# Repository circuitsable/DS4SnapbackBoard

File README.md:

# DS4SnapbackBoard

This is a PCB that latches onto the bottom of your joysticks on a DualShock 4 intended to get rid of controller snapback.

# Why/About

Never heard of snapback? Here is a [video](https://www.youtube.com/watch?v=O4rigBTxgPM) describing it and why it is a problem.

I designed this because several of my DS4 controllers have had issues with snapback and the issues it entails, and because I prefered a cleaner result than through hole ceramic capacitors lying on the back of my controller's PCB. It connects the signal & ground pins of each axis' potentiometer to dampen the oscillations of the snapback.

This mod uses 0805 1uF ceramic SMD capacitors, since I wanted to make the capacitors somewhat easy to install and 1uF is a good catchall value to stop snapback. Different boards for different capacitor sizes can very easily be made, make an issue for a different size if you would like one.

This mod should not require much experience soldering, but if the capacitor size is too small, create an issue on this repo requesting a bigger size. Editing the PCB yourself to use bigger capacitors should be very easy as well.

# What you'll need

The PCB, of which gerbers are available for in the [releases](https://github.com/circuitsable/DS4SnapbackBoard/releases/tag/gerbers). The thinner you can make the PCB, the better, 0.8mm is a good thickness. The PCB can be ordered from any board house, but some may not like the castellated holes or charge extra for them. [Oshpark](https://oshpark.com/#services) will do castilated holes, has 0.8mm availability and is quite cheap, but the finished boards may require post processing with a small knife.

2 0805 1uF SMD Ceramic Capacitors. Their voltage rating does not matter. They can be sourced from anywhere, here are some examples: [Aliexpress](https://www.aliexpress.us/item/2251832778239041.html), [Ebay](https://www.ebay.com/itm/195680390537), [Mouser](https://www.mouser.com/ProductDetail/Samsung-Electro-Mechanics/CL21B105KPFNNNE?qs=349EhDEZ59rb3V94UrmRdQ%3D%3D)

Basic soldering equipment.

Hobby knife.

# Installation

Touch up the castilated holes of your PCB, as they will most certainly arrive with excess material from the pads being drilled. Solder the capacitors to their two available footprints on the PCB, align the PCB in the middle of the joystick footprint on the back of your DS4 board, solder the 4 big pads first to keep the board in alignment, then solder the pads to the actual potentiometer legs of the joysticks.

# PCB Images

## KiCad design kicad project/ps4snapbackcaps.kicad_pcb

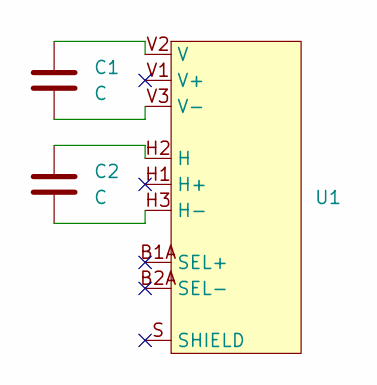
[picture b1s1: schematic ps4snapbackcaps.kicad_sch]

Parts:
C1, C2: C; C_0805_2012Metric_Pad1.18x1.45mm_HandSolder
U1: PS4_joystick

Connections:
unnamed: C2.1, U1.H2 (H)
unnamed: C2.2, U1.H3 (H-)
unnamed: C1.1, U1.V2 (V)
unnamed: C1.2, U1.V3 (V-)

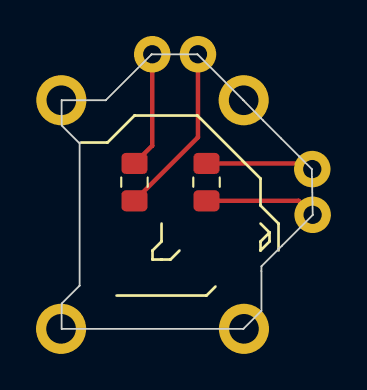
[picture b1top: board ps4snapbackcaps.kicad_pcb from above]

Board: 2 copper layers, 14.0 x 15.2 mm, 3 parts (1 on the bottom side), 4 nets.

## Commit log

2024-04-14 Update ReadMe again
2024-04-14 Added images
2024-04-14 Update ReadMe to actually display images
2024-04-14 Add more images
2024-04-14 update images
2024-04-14 add gerbers
2024-04-14 add kicad design filex
2024-04-14 update kicad design files
2024-04-16 update gerbers
2024-04-30 all images
2024-10-27 erm... oops!
2024-10-27 oopsie!
2024-10-27 oops haha!
2024-10-27 goops!
2024-10-27 goopsies!
